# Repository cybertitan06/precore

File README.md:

# Pre-CORE 2025

Welcome! Pre-CORE is an Air Force hosted training program to get members up to speed on development topics before entering the CORE training pipeline. This is to ensure that individuals coming from staff/administrative/leadership jobs have the opportunity to brush up prior to the CORE training firehose.

## Schedule

The calendar is [viewable online here](https://docs.google.com/spreadsheets/d/18q04ph0zQdPjvAenrT8Udl4wduihoQtP5SdtEu-uExw/edit?usp=sharing) and is provided here below:

## Location

Pre-CORE 2025 will be held in the following locations over the following dates:

**Maritime Conference Center**<br/>
692 Maritime Blvd<br/>
Linthicum Heights, MD 21090<br/>

- May 27 to July 3: Classroom 1

Click [here](resources/mcc_property.pdf) for directions and a building layout.

## Requirements

- Students are required to bring a personal laptop for training.
  - Student environments should be x86/x86_64 (or emulate it appropriately).
  - **ARM processors, such as the M1, are not fully supported by the course content at this time. Cross-compilation is used to produce x86/x64 binaries**.
  - Student laptops should support WiFi and handle a 2 vCPU/4GB RAM virtual machine.

## Pre-Made Virtual Machine

The following virtual machine isn't required but we have put in tools you will need into one image. Download it before Day 1 of Pre-CORE and we can help you set it up.

- username: student
- password: precore

- [x86_64 Intel Processor Image (WIP)](https://drive.google.com/file/d/1MsmbaFYyNup1oGJvcaY-5MyzUSOQr0M-/view?usp=sharing) - This image will work for both VMWare and VirtualBox. However, VMWare is more performant.

## Custom Setup

- If you are comfortable setting up a C/Python/Assembly workflow of your own, you are able to use your own environment.

  - [Recommended Installed Items](resources/RecommendedEnvironment.md)

## Course Materials

- Please clone this repository to your environment prior to Pre-CORE
- The course slides are [available here](https://drive.google.com/drive/folders/1UE_-xn_uqygakUEzAAoSwDveC04yUQbJ?usp=sharing)

## Dress Policy

- For military members: Civilian Clothes unless otherwise specified on the calendar. All members are encouraged to dress as though this were external/vendor training.

## Discord

[Join the Pre-CORE Discord](https://discord.gg/c3hpKt38jZ) to receive announcements and class materials throughout the course.

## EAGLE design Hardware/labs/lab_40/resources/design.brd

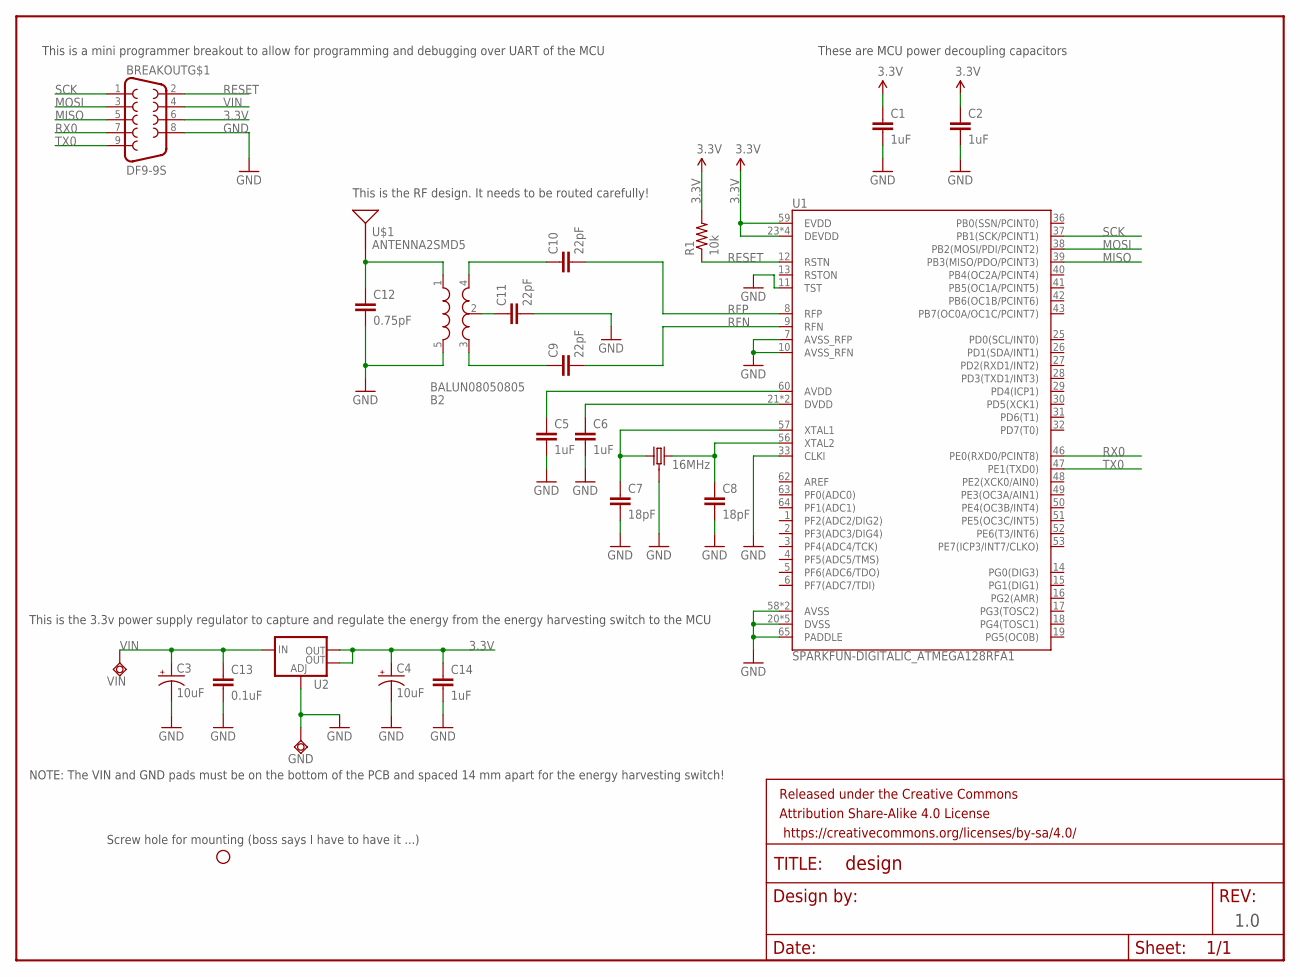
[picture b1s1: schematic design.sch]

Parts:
B2: BALUN08050805; BALUN0805
BREAKOUT: DF9-9S
C1, C2, C5, C6, C14: 1uF; 0603-CAP
C3, C4: 10uF; EIA3216
C7, C8: 18pF; 0603-CAP
C9, C10: 22pF; C0402
C11: 22pF; 0603-CAP
C12: 0.75pF; 0603-CAP
C13: 0.1uF; 0603-CAP
FRAME1: FRAME-LETTERNO_PACKAGE; DUMMY
GND: TPSQTP20SQ; TP20SQ
H1: STAND-OFF
R1: 10k; 0603-RES
U1: SPARKFUN-DIGITALIC_ATMEGA128RFA1; SPARKFUN-DIGITALIC_QFN-64
U2: V_REG_LM1117SOT223; SOT223
U$1: ANTENNA2SMD5; ANTENNA-CHIP5
VIN: TPSQTP20SQ; TP20SQ
Y2: 16MHz; SPARKFUN-FREQCTRL_CRYSTAL-SMD-5X3

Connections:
3.3V: BREAKOUT.6, C1.1, C2.1, C4.A (+), C14.1, R1.2, U1.23 (DEVDD), U1.34 (DEVDD), U1.44 (DEVDD), U1.54 (DEVDD), U1.59 (EVDD), U2.2 (OUT), U2.4 (OUT)
GND: B2.5 (GND), BREAKOUT.8, C1.2, C2.2, C3.C (-), C4.C (-), C5.2, C6.2, C7.2, C8.2, C11.2, C12.2, C13.2, C14.2, GND.TP, U1.7 (AVSS_RFP), U1.10 (AVSS_RFN), U1.11 (TST), U1.20 (DVSS), U1.24 (DVSS), U1.33 (CLKI), U1.35 (DVSS), U1.45 (DVSS), U1.55 (DVSS), U1.58 (AVSS), U1.61 (AVSS), U1.65 (PADDLE), U2.1 (ADJ), Y2.2 (3), Y2.4 (3)
MISO: BREAKOUT.5, U1.39 (PB3(MISO/PDO/PCINT3))
MOSI: BREAKOUT.3, U1.38 (PB2(MOSI/PDI/PCINT2))
unnamed: C5.1, U1.60 (AVDD)
unnamed: C6.1, U1.21 (DVDD), U1.22 (DVDD)
unnamed: C8.1, U1.56 (XTAL2), Y2.3 (2)
unnamed: C7.1, U1.57 (XTAL1), Y2.1
unnamed: B2.2 (GND), C11.1
unnamed: B2.3 (OUT2), C9.1
unnamed: B2.4 (OUT1), C10.1
unnamed: B2.1 (IN), C12.1, U$1.FEED
RESET: BREAKOUT.2, R1.1, U1.12 (RSTN)
RFN: C9.2, U1.9 (RFN)
RFP: C10.2, U1.8 (RFP)
RX0: BREAKOUT.7, U1.46 (PE0(RXD0/PCINT8))
SCK: BREAKOUT.1, U1.37 (PB1(SCK/PCINT1))
TX0: BREAKOUT.9, U1.47 (PE1(TXD0))
VIN: BREAKOUT.4, C3.A (+), C13.1, U2.3 (IN), VIN.TP

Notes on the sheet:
1.0
This is the 3.3v power supply regulator to capture and regulate the energy from the energy harvesting switch to the MCU
Screw hole for mounting (boss says I have to have it ...)
These are MCU power decoupling capacitors
This is the RF design. It needs to be routed carefully!
This is a mini programmer breakout to allow for programming and debugging over UART of the MCU
NOTE: The VIN and GND pads must be on the bottom of the PCB and spaced 14 mm apart for the energy harvesting switch!

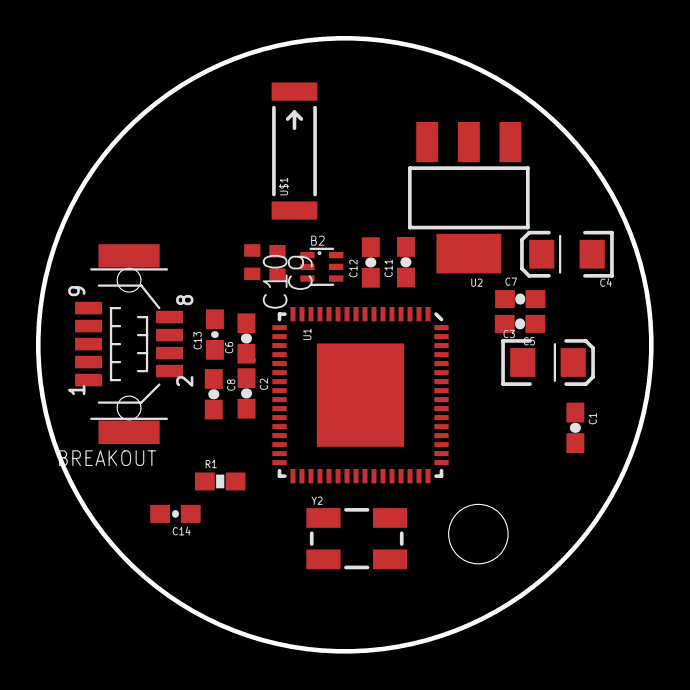
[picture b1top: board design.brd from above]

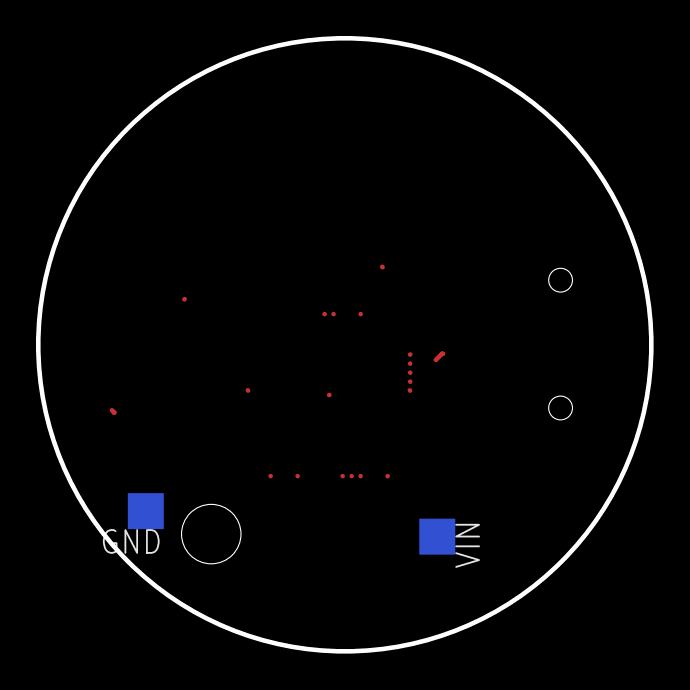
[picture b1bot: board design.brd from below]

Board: 2 copper layers, 34.1 x 34.1 mm, 25 parts (2 on the bottom side), 19 nets.

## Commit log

2025-05-20 Initial Commit For Student Repo
2025-05-28 Logic bug in systests
2025-05-29 Update bitwise_and.c
    Removed bad check
2025-05-30 Sign in Script
2025-05-31 Testing ability to push/pull changes from home pc to laptop and vice-versa for a third time
2025-06-01 Adding updated sleep & hostname functions
2025-06-01 Sending updated functions
2025-06-02 Adding changes from laptop vm
2025-06-03 Updating with most recent function files
2025-06-03 Updated connect_to_server function
2025-06-04 Adding server python files
2025-06-05 Added server function list to ease lookup efforts
2025-06-05 Began loading pseudocode into the manage_agent function
2025-06-05 Updated server function & connection_cb
2025-06-06 Updated server files and client commands
2025-06-08 Mostly finished deserialization_command, began working on recieve_command
2025-06-09 Updated parse response and ACME server
2025-06-10 Adding ASM_RE files
2025-06-11 Added challenge problem and directory.
2025-06-11 Finished day 1 debugging examples, started on fitb labs
2025-06-12 Finished most of day1 exercises, started on day1.5 broken exercises
2025-06-12 Finished day3 ex 1-6
2025-06-13 Updated labs and structure to 2025 version
2025-06-13 Updated guidance for buffer overlfow ex01
2025-06-15 Took another stab at buffer overflows
2025-06-16 Added basic overflow
2025-06-17 Staging for crypto labs
2025-06-17 remote
2025-06-17 Update fitb05.asm
    This has been wrong for years. It compares the address, when it should compare the value at the address. Shoutout Delta (and Daniel the student)!
2025-06-17 Adding crypto labs and updates to recieve and deserialize commands
2025-06-18 merging branches
2025-06-18 Removed bug, added another
2025-06-18 Debugging seg faults in deserialization command
2025-06-18 A commented solution to help with the lab
2025-06-18 Updated RoadRunner functions, began working on interactions with ACME
2025-06-20 Updating HW labs
2025-06-23 resetting for Monday
2025-06-23 Adding esp32 wifi code
2025-06-26 Added ssh docker example
2025-06-26 Capstone wireguard config

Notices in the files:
parts and their libraries:
SparkFun-Passives: Licensing: Creative Commons ShareAlike 4.0 International - https://creativecommons.org/licenses/by-sa/4.0
SparkFun-Aesthetics: Released under the Creative Commons Attribution Share-Alike 4.0 License
SparkFun-Aesthetics: https://creativecommons.org/licenses/by-sa/4.0
